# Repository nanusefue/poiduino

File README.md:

# poiduino

Material

Dremel
Brocas para pcb
Cables
Estanio
Soldadores
Grabador avr
Protector Circuitos
Toner 
Impresora
Papel Fotografico
Productos quimicos
Placas cobre

Plancha
Alcohol
Guantes

papel de diario

<<<<<<< HEAD

http://eagle.autodesk.com/eagle/software-versions
=======
Papel para transfer de placas PCB
Alicate
>>>>>>> a70d30c0ad49bb2c235c82a74168aaa96ec9a255

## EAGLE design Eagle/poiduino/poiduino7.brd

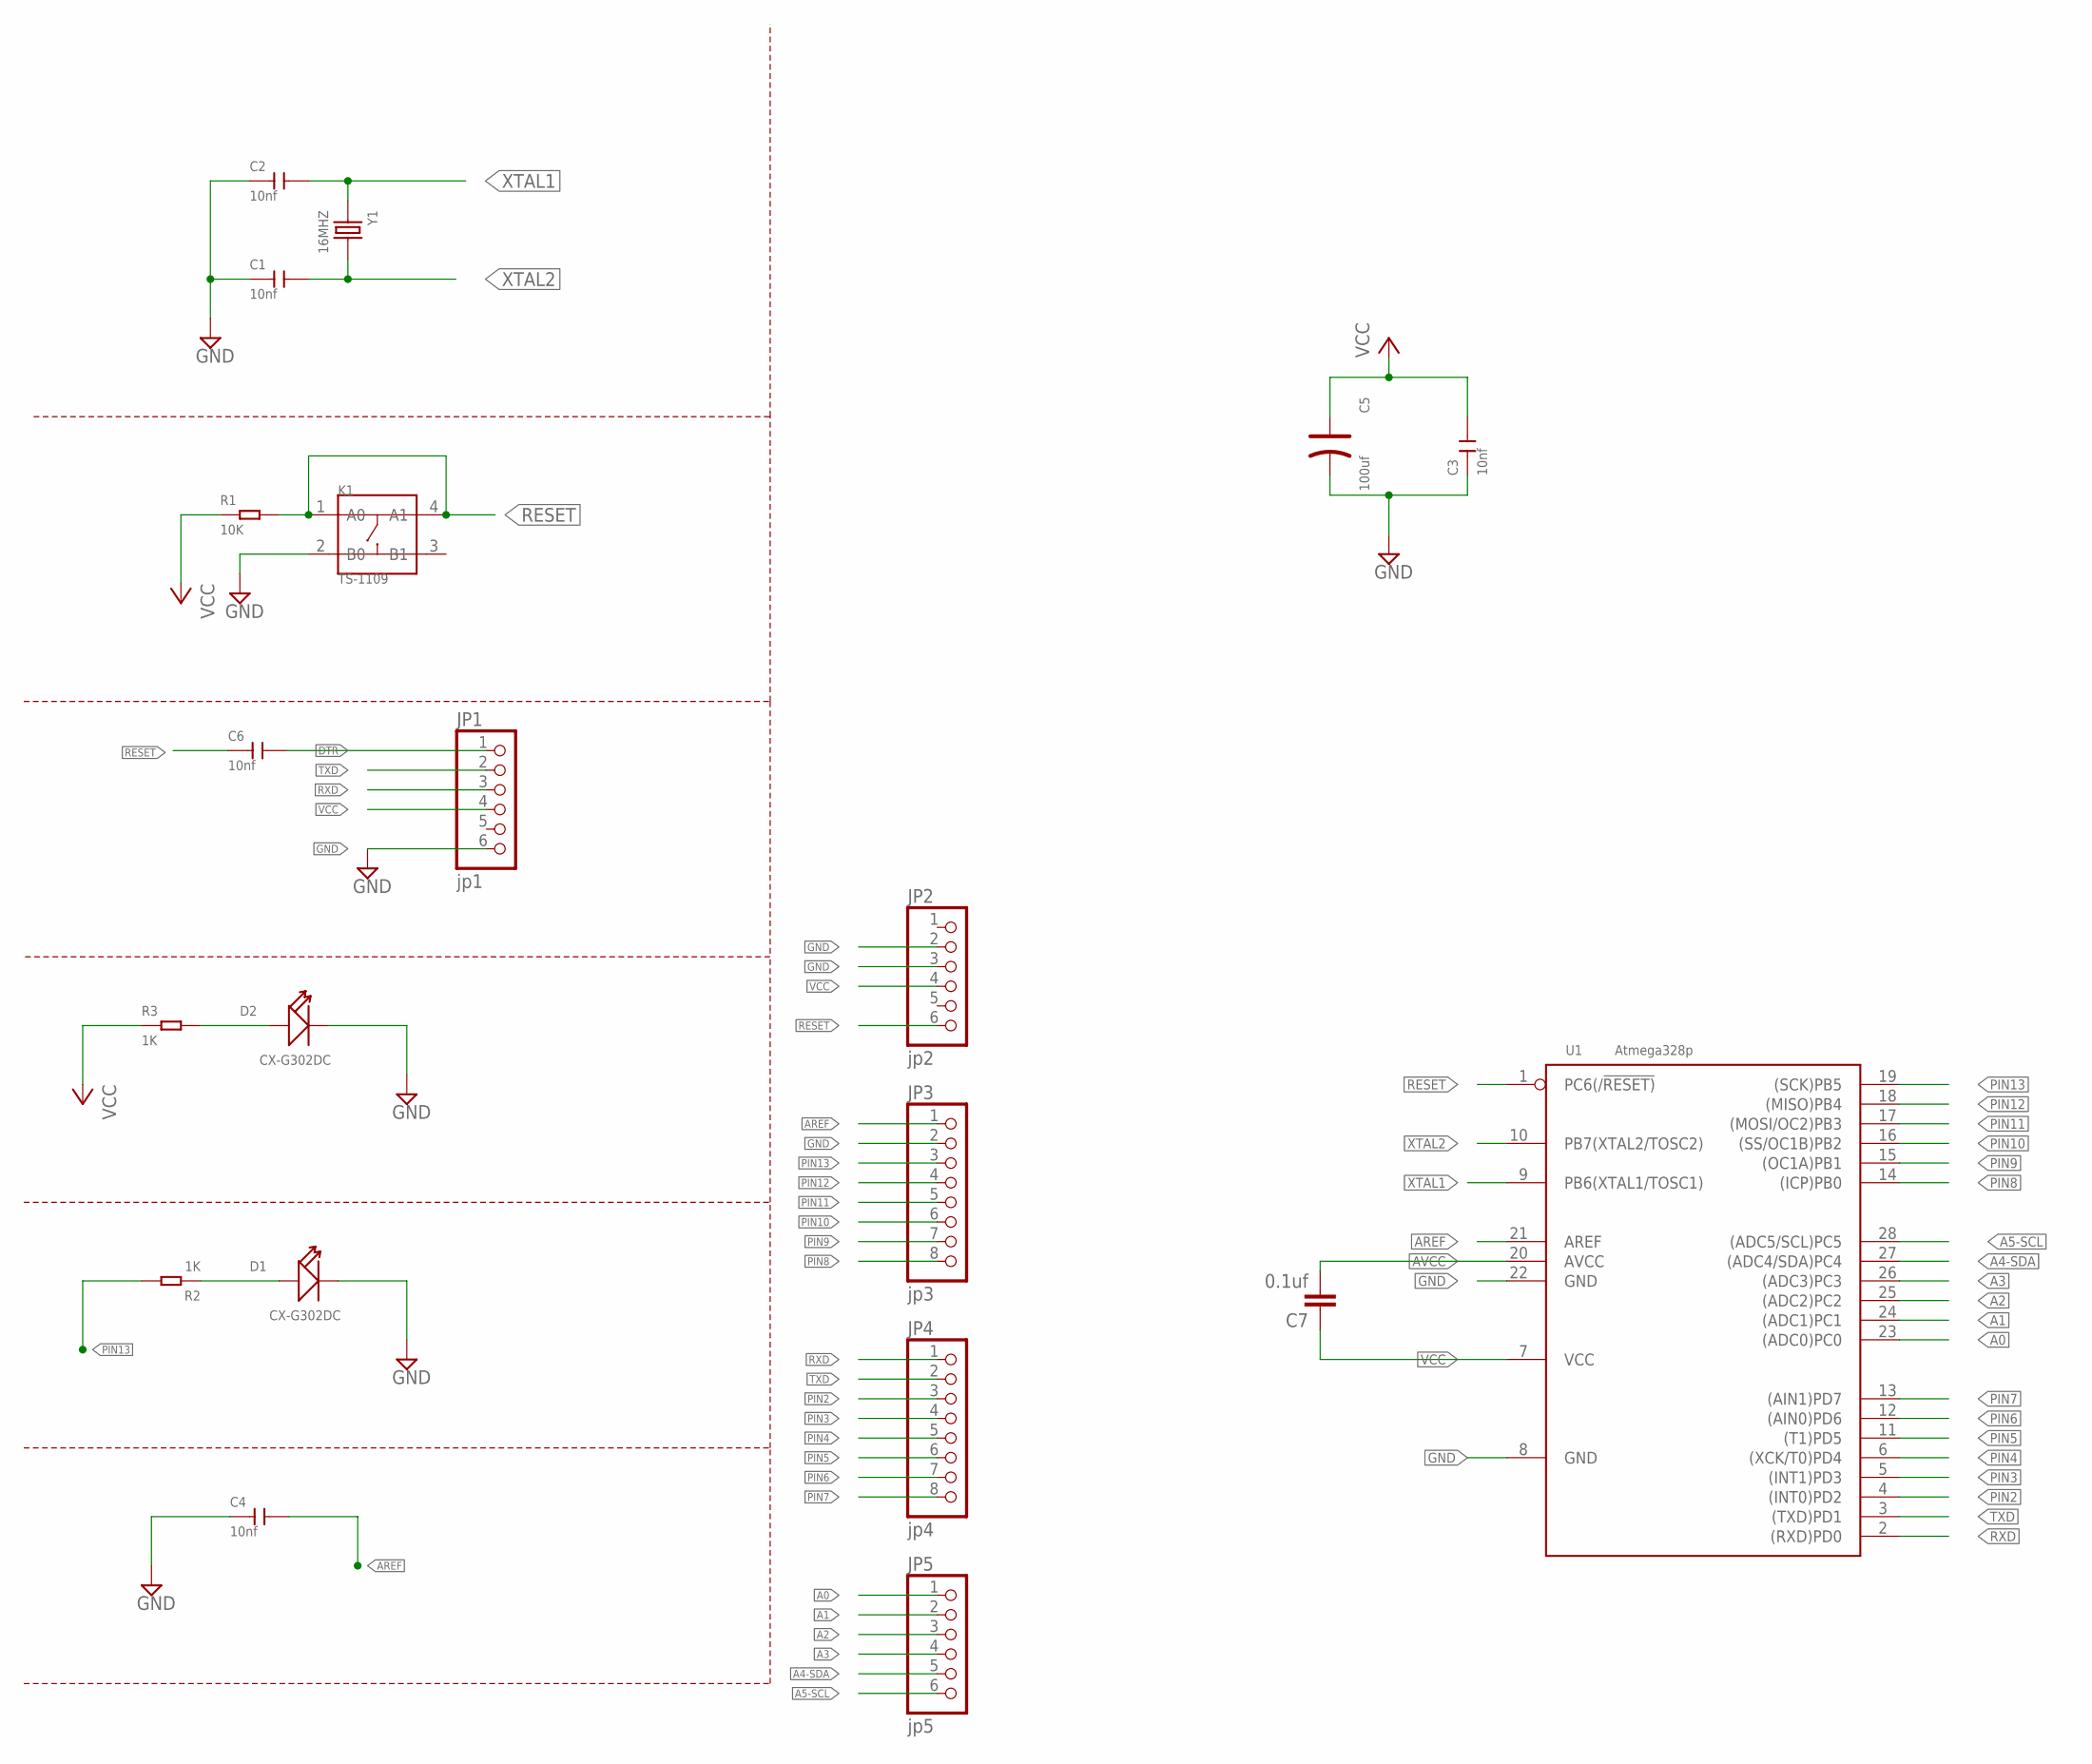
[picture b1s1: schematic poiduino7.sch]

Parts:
C1, C2, C3, C4, C6: 10nf; CERAMIC-2.54
C5: 100uf; PC-D5.3MM
C7: 0.1uf; C5B2.5
D1, D2: CX-G302DC; LED2-2.54-D3.0MM
JP1: jp1; 1X06
JP2: jp2; 1X06
JP3: jp3; 1X08
JP4: jp4; 1X08
JP5: jp5; 1X06
K1: TS-1109; SW4-6.0X6.0X5.0MM
R1: 10K; PR-D2.3XL6.5MM
R2, R3: 1K; PR-D2.3XL6.5MM
U1: Atmega328p; DIP28-2.54-34.7X7.62MM
Y1: 16MHZ; HC49US

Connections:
A0: JP5.1, U1.23 ((ADC0)PC0)
A1: JP5.2, U1.24 ((ADC1)PC1)
A2: JP5.3, U1.25 ((ADC2)PC2)
A3: JP5.4, U1.26 ((ADC3)PC3)
A4-SDA: JP5.5, U1.27 ((ADC4/SDA)PC4)
A5-SCL: JP5.6, U1.28 ((ADC5/SCL)PC5)
AREF: C4.2, JP3.1, U1.21 (AREF)
AVCC: C7.2, U1.20 (AVCC)
DTR: C6.2, JP1.1
GND: C1.1, C2.1, C3.1, C4.1, C5.-, D1.K (-), D2.K (-), JP1.6, JP2.2, JP2.3, JP3.2, K1.2 (B0), U1.8 (GND), U1.22 (GND)
unnamed: D2.A (+), R3.2
unnamed: D1.A (+), R2.1
PIN2: JP4.3, U1.4 ((INT0)PD2)
PIN3: JP4.4, U1.5 ((INT1)PD3)
PIN4: JP4.5, U1.6 ((XCK/T0)PD4)
PIN5: JP4.6, U1.11 ((T1)PD5)
PIN6: JP4.7, U1.12 ((AIN0)PD6)
PIN7: JP4.8, U1.13 ((AIN1)PD7)
PIN8: JP3.8, U1.14 ((ICP)PB0)
PIN9: JP3.7, U1.15 ((OC1A)PB1)
PIN10: JP3.6, U1.16 ((SS/OC1B)PB2)
PIN11: JP3.5, U1.17 ((MOSI/OC2)PB3)
PIN12: JP3.4, U1.18 ((MISO)PB4)
PIN13: JP3.3, R2.2, U1.19 ((SCK)PB5)
RESET: C6.1, JP2.6, K1.1 (A0), K1.4 (A1), R1.2, U1.1 (PC6(/!RESET))
RXD: JP1.3, JP4.1, U1.2 ((RXD)PD0)
TXD: JP1.2, JP4.2, U1.3 ((TXD)PD1)
VCC: C3.2, C5.+, C7.1, JP1.4, JP2.4, R1.1, R3.1, U1.7 (VCC)
XTAL1: C2.2, U1.9 (PB6(XTAL1/TOSC1)), Y1.1
XTAL2: C1.2, U1.10 (PB7(XTAL2/TOSC2)), Y1.2

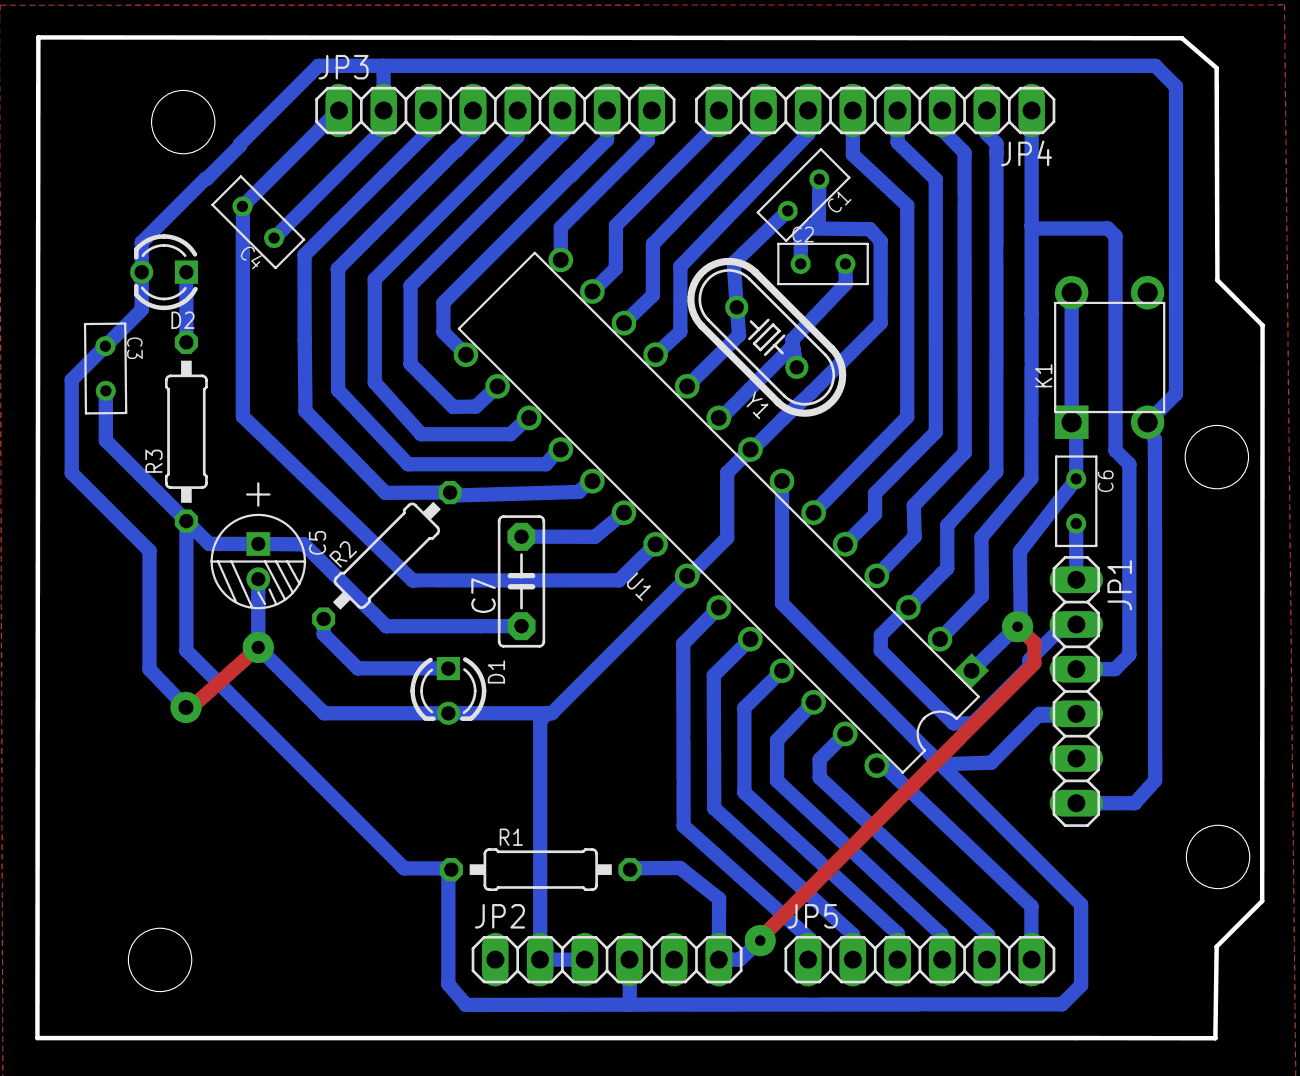
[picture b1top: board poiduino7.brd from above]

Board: 2 copper layers, 69.6 x 56.9 mm, 20 parts (0 on the bottom side), 30 nets.

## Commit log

2018-06-20 add gitignore and new board
2018-06-20 new board
2018-06-21 add more materials
2018-06-24 rename file and folders, generate gcode and simulate files for Roland
2018-06-24 custom cam for tonner method
2018-07-02 test
2018-07-04 fix pads board
2018-07-08 add pad more sizes
2018-07-08 refactor folder
2018-07-08 remove poligono de corte exterior
2018-07-10 nueva lib
2018-07-10 lista componentes
2018-07-10 add lib
2018-07-10 sw lbr
